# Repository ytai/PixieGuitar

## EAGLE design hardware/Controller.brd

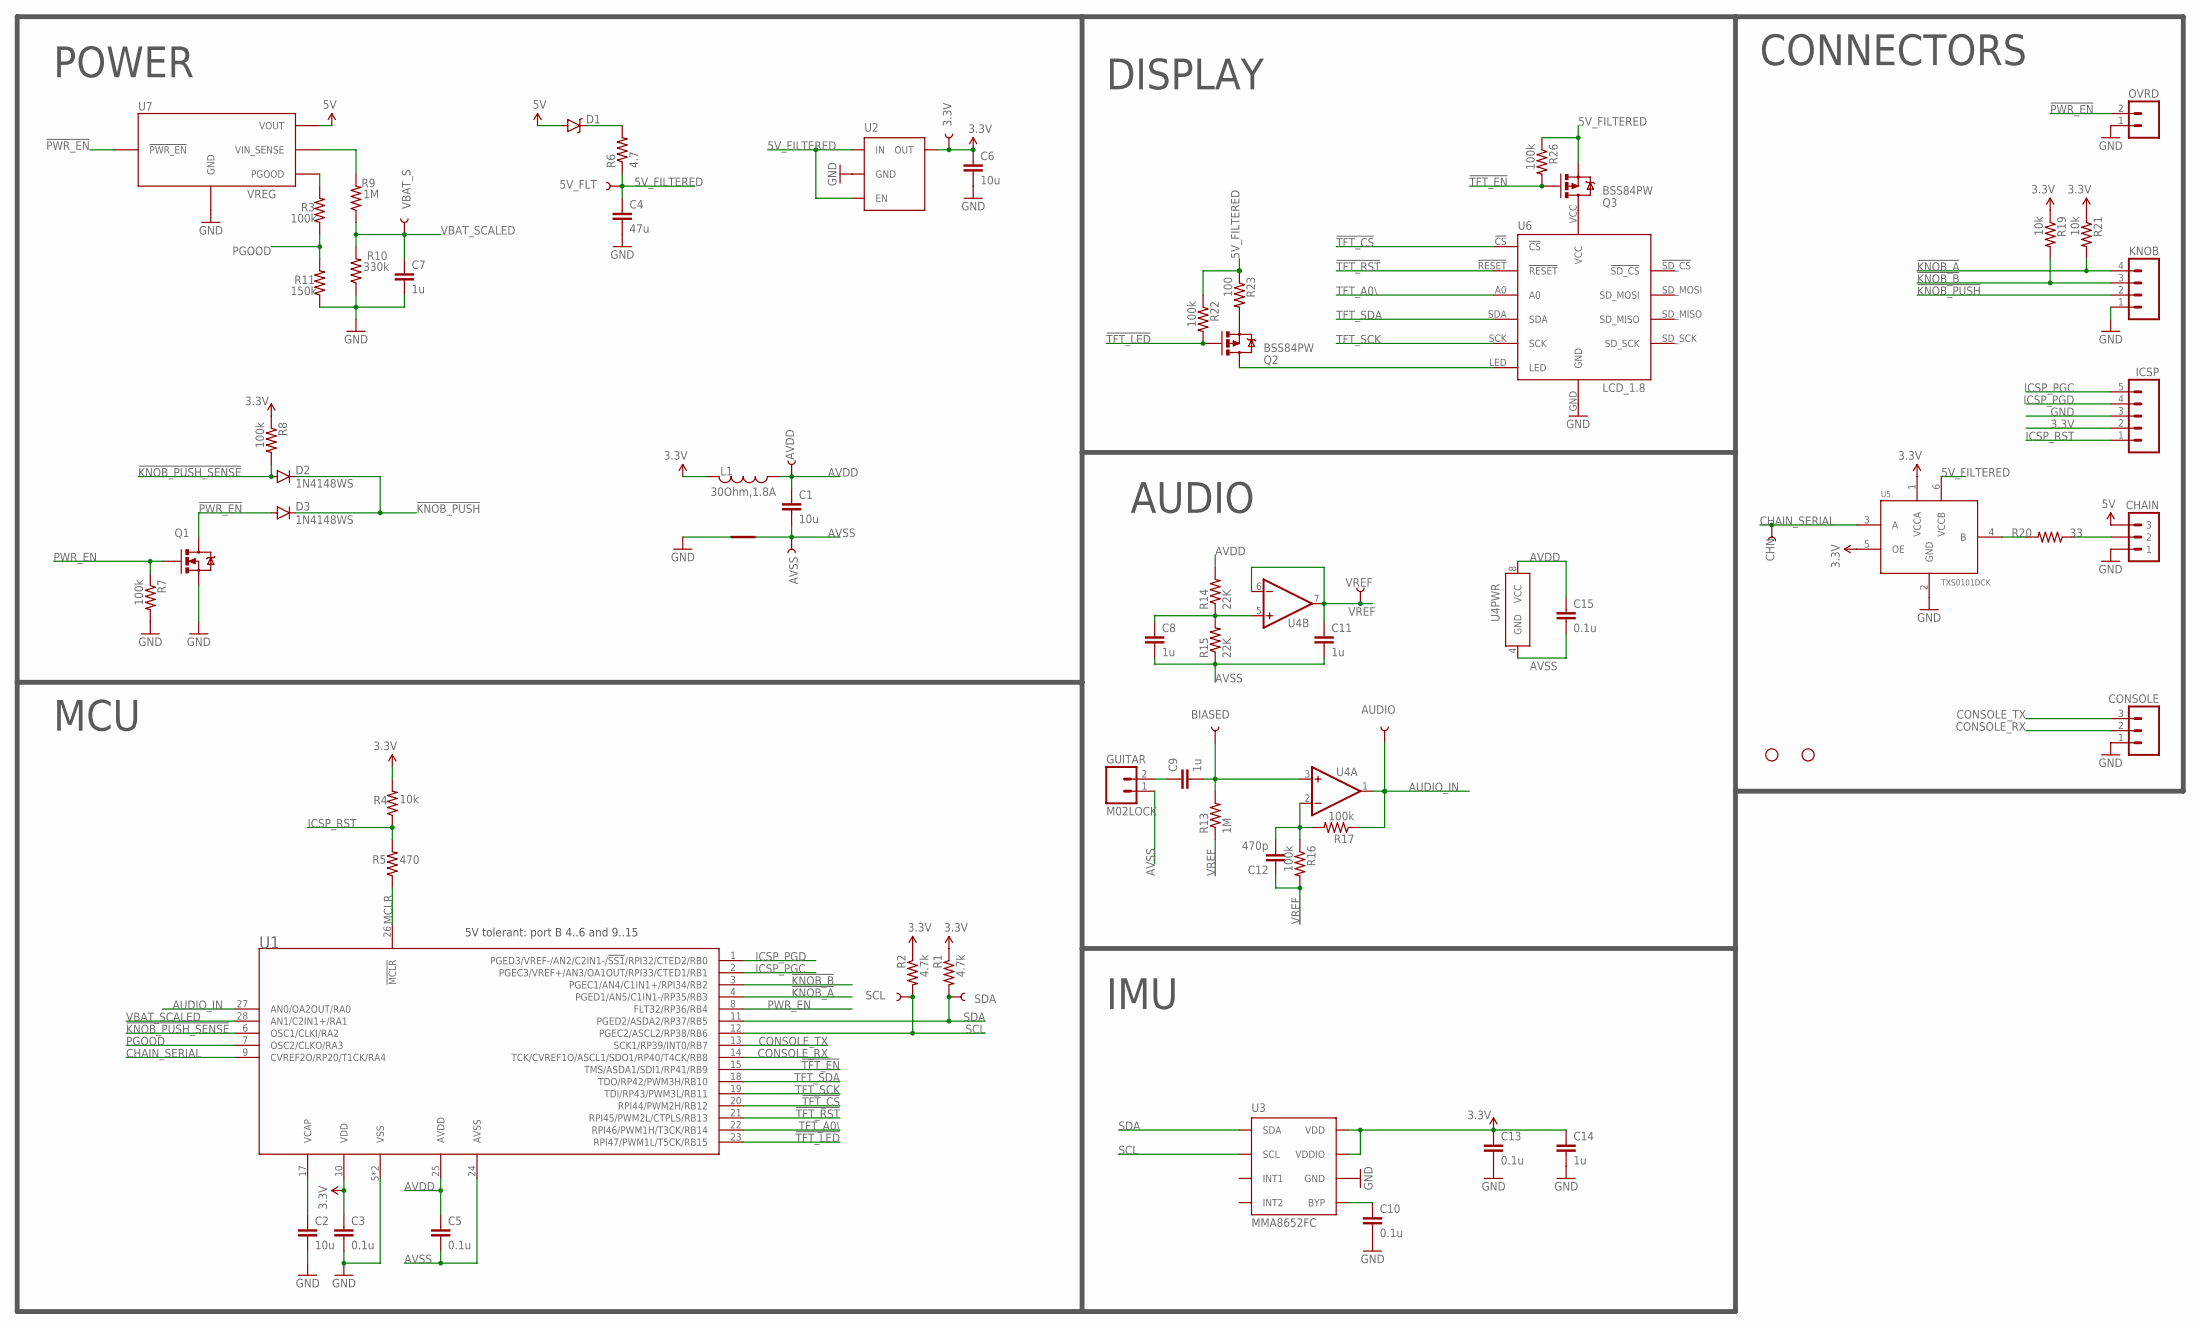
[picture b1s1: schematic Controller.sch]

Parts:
3.3V, 5V_FLT: TEST-POINT3; PAD.03X.03
AUDIO: TEST-POINT3; PAD.03X.03
AVDD: TEST-POINT3; PAD.03X.03
AVSS: TEST-POINT3; PAD.03X.03
BIASED: TEST-POINT3; PAD.03X.03
C1, C2: 10u; 0805
C3, C5, C10, C13, C15: 0.1u; 0603-CAP
C4: 47u; 1206
C6: 10u; 0603-CAP
C7, C8, C9, C11, C14: 1u; 0603-CAP
C12: 470p; 0603-CAP
CHAIN: M030.1PWR+SIG; 1X03-0.1PWR+SIG
CHN: TEST-POINT3; PAD.03X.03
CONSOLE: M03LOCK; 1X03_LOCK
D1: DB2J20900L; SOD-323
D2, D3: 1N4148WS; SOD-323
GUITAR: M02LOCK; 1X02_LOCK
ICSP: M05LOCK; 1X05_LOCK
JP1, JP2: STAND-OFF
KNOB: M04LOCK; 1X04_LOCK
L1: 30Ohm,1.8A; 0603
OVRD: M02LOCK; 1X02_LOCK
Q1: MOSFET-NCHANNEL2N7002PW; SOT323
Q2, Q3: BSS84PW; SOT323
R1, R2: 4.7k; 0603-RES
R3, R7, R8, R16, R17, R22, R26: 100k; 0603-RES
R4, R19, R21: 10k; 0603-RES
R5: 470; 0603-RES
R6: 4.7; 0603-RES
R9, R13: 1M; 0603-RES
R10: 330k; 0603-RES
R11: 150k; 0603-RES
R14, R15: 22K; 0603-RES
R20: 33; 0603-RES
R23: 100; 0603-RES
SCL: TEST-POINT3; PAD.03X.03
SDA: TEST-POINT3; PAD.03X.03
SH1: SHORT; SHORT_TOP-8
U1: DSPIC33EPXXXMC202/502/PT; QFN-S-28
U2: MIC5365YC5; SC70
U3: MMA8652FC; 10-VFDFN
U4: MCP6002MS; MSOP-8
U5: TXS0101DCK; SC70-6
U6: LCD_1.8
U7: VREG
VBAT_S: TEST-POINT3; PAD.03X.03
VREF: TEST-POINT3; PAD.03X.03

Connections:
3.3V: 3.3V.P$1, C3.1, C6.1, C13.1, C14.1, ICSP.2, L1.2, R1.1, R2.1, R4.2, R8.1, R19.1, R21.1, U1.10 (VDD), U2.5 (OUT), U3.1 (VDD), U3.8 (VDDIO), U5.1 (VCCA), U5.5 (OE)
5V: CHAIN.P$3 (3), D1.A, U7.VOUT
5V_FILTERED: 5V_FLT.P$1, C4.1, Q3.2 (S), R6.1, R22.1, R23.1, R26.1, U2.1 (IN), U2.3 (EN), U5.6 (VCCB)
!KNOB_A: KNOB.4, R21.2, U1.4 (PGED1/AN5/C1IN1-/RP35/RB3)
!KNOB_B: KNOB.3, R19.2, U1.3 (PGEC1/AN4/C1IN1+/RPI34/RB2)
!KNOB_PUSH: D2.C, D3.C, KNOB.2
!KNOB_PUSH_SENSE: D2.A, R8.2, U1.6 (OSC1/CLKI/RA2)
!PWR_EN: D3.A, OVRD.2, Q1.3 (D), U7.!EN (!PWR_EN)
!TFT_CS: U1.20 (RPI44/PWM2H/RB12), U6.!CS
!TFT_EN: Q3.1 (G), R26.2, U1.15 (TMS/ASDA1/SDI1/RP41/RB9)
!TFT_LED: Q2.1 (G), R22.2, U1.23 (RPI47/PWM1L/T5CK/RB15)
!TFT_RST: U1.21 (RPI45/PWM2L/CTPLS/RB13), U6.!RESET
AUDIO_IN: AUDIO.P$1, R17.1, U1.27 (AN0/OA2OUT/RA0), U4.1 (OUT)
AVDD: AVDD.P$1, C1.1, C5.1, C15.1, L1.1, R14.2, U1.25 (AVDD), U4.8 (VCC)
AVSS: AVSS.P$1, C1.2, C5.2, C8.2, C11.2, C15.2, GUITAR.1, R15.1, SH1.2, U1.24 (AVSS), U4.4 (GND)
CHAIN_SERIAL: CHN.P$1, U1.9 (CVREF2O/RP20/T1CK/RA4), U5.3 (A)
CONSOLE_RX: CONSOLE.2, U1.14 (TCK/CVREF1O/ASCL1/SDO1/RP40/T4CK/RB8)
CONSOLE_TX: CONSOLE.3, U1.13 (SCK1/RP39/INT0/RB7)
GND: C2.2, C3.2, C4.2, C6.2, C7.2, C10.2, C13.2, C14.2, CHAIN.P$1 (1), CONSOLE.1, ICSP.3, KNOB.1, OVRD.1, Q1.2 (S), R7.2, R10.1, R11.1, SH1.1, U1.5 (VSS), U1.16 (VSS), U2.2 (GND), U3.6 (GND), U3.7 (GND), U3.9 (GND), U5.2 (GND), U6.GND, U7.GND_OUT (GND)
ICSP_PGC: ICSP.5, U1.2 (PGEC3/VREF+/AN3/OA1OUT/RPI33/CTED1/RB1)
ICSP_PGD: ICSP.4, U1.1 (PGED3/VREF-/AN2/C2IN1-/!SS1!/RPI32/CTED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)
ICSP_RST: ICSP.1, R4.1, R5.2
MCLR: R5.1, U1.26 (!MCLR)
unnamed: C8.1, R14.1, R15.2, U4.5 (+IN)
unnamed: D1.C, R6.2
unnamed: C9.1, GUITAR.2
unnamed: C12.2, R16.1, R17.2, U4.2 (-IN)
unnamed: C2.1, U1.17 (VCAP)
unnamed: R20.2, U5.4 (B)
unnamed: BIASED.P$1, C9.2, R13.2, U4.3 (+IN)
unnamed: R3.2, U7.PGOOD
unnamed: Q2.3 (D), U6.LED
unnamed: Q3.3 (D), U6.VCC
unnamed: Q2.2 (S), R23.2
unnamed: C10.1, U3.4 (BYP)
unnamed: CHAIN.P$2 (2), R20.1
PGOOD: R3.1, R11.2, U1.7 (OSC2/CLKO/RA3)
PWR_EN: Q1.1 (G), R7.1, U1.8 (FLT32/RP36/RB4)
SCL: R2.2, SCL.P$1, U1.12 (PGEC2/ASCL2/RP38/RB6), U3.2 (SCL)
SDA: R1.2, SDA.P$1, U1.11 (PGED2/ASDA2/RP37/RB5), U3.10 (SDA)
TFT_A0\: U1.22 (RPI46/PWM1H/T3CK/RB14), U6.A0
TFT_SCK: U1.19 (TDI/RP43/PWM3L/RB11), U6.SCK
TFT_SDA: U1.18 (TDO/RP42/PWM3H/RB10), U6.SDA
VBAT_SCALED: C7.1, R9.1, R10.2, U1.28 (AN1/C2IN1+/RA1), VBAT_S.P$1
VBAT_SENSE: R9.2, U7.VSENSE (VIN_SENSE)
VREF: C11.1, C12.1, R13.1, R16.2, U4.6 (-IN), U4.7 (OUT), VREF.P$1

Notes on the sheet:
5V tolerant: port B 4..6 and 9..15
POWER
IMU
AUDIO
DISPLAY
CONNECTORS
MCU

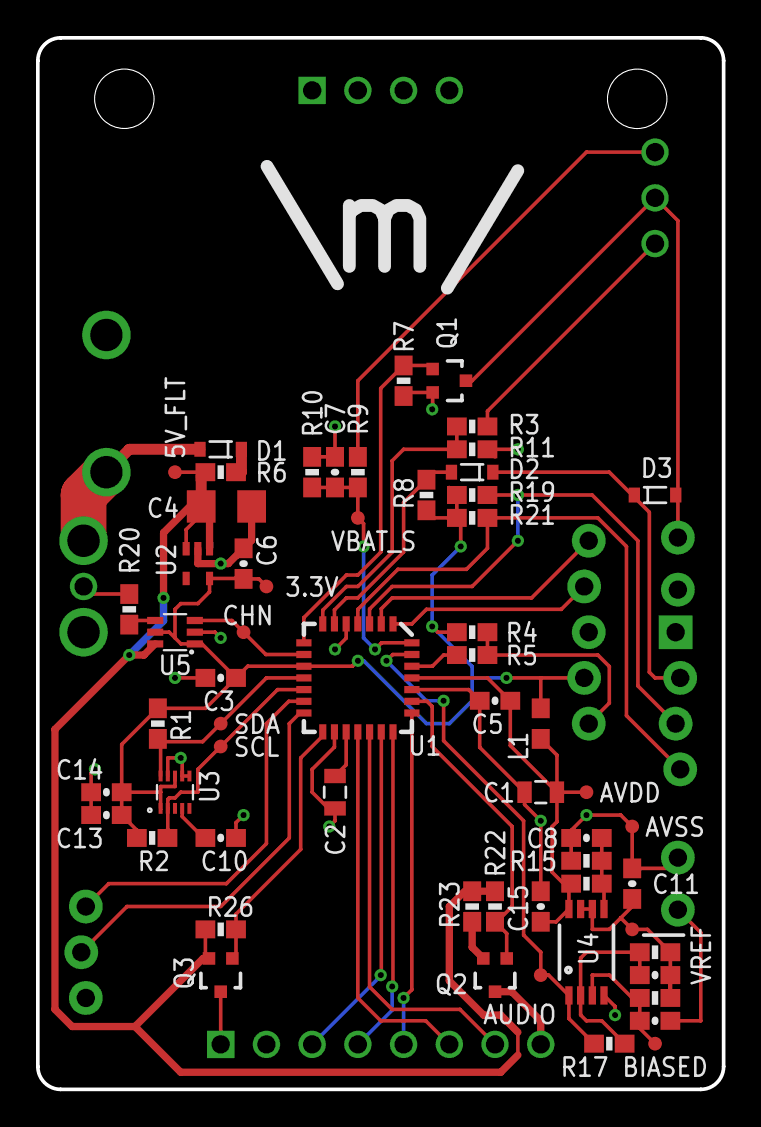
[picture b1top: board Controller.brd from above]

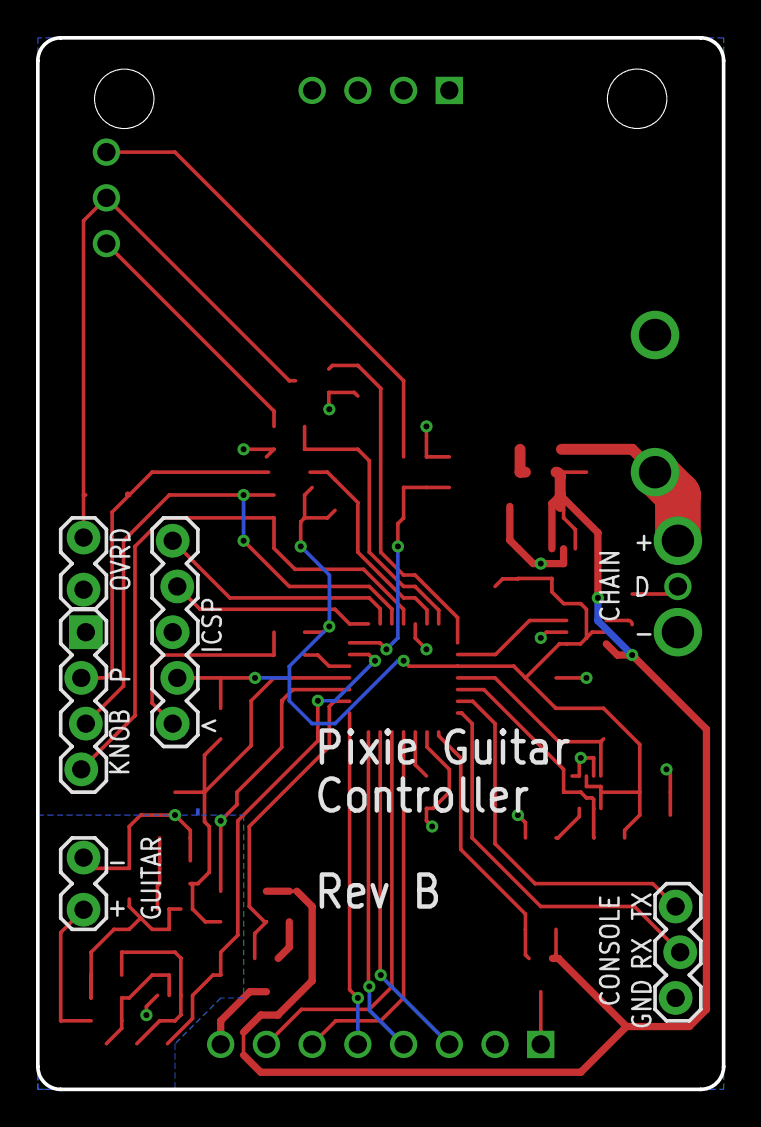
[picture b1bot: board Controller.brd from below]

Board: 2 copper layers, 38.1 x 58.4 mm, 71 parts (8 on the bottom side), 46 nets.

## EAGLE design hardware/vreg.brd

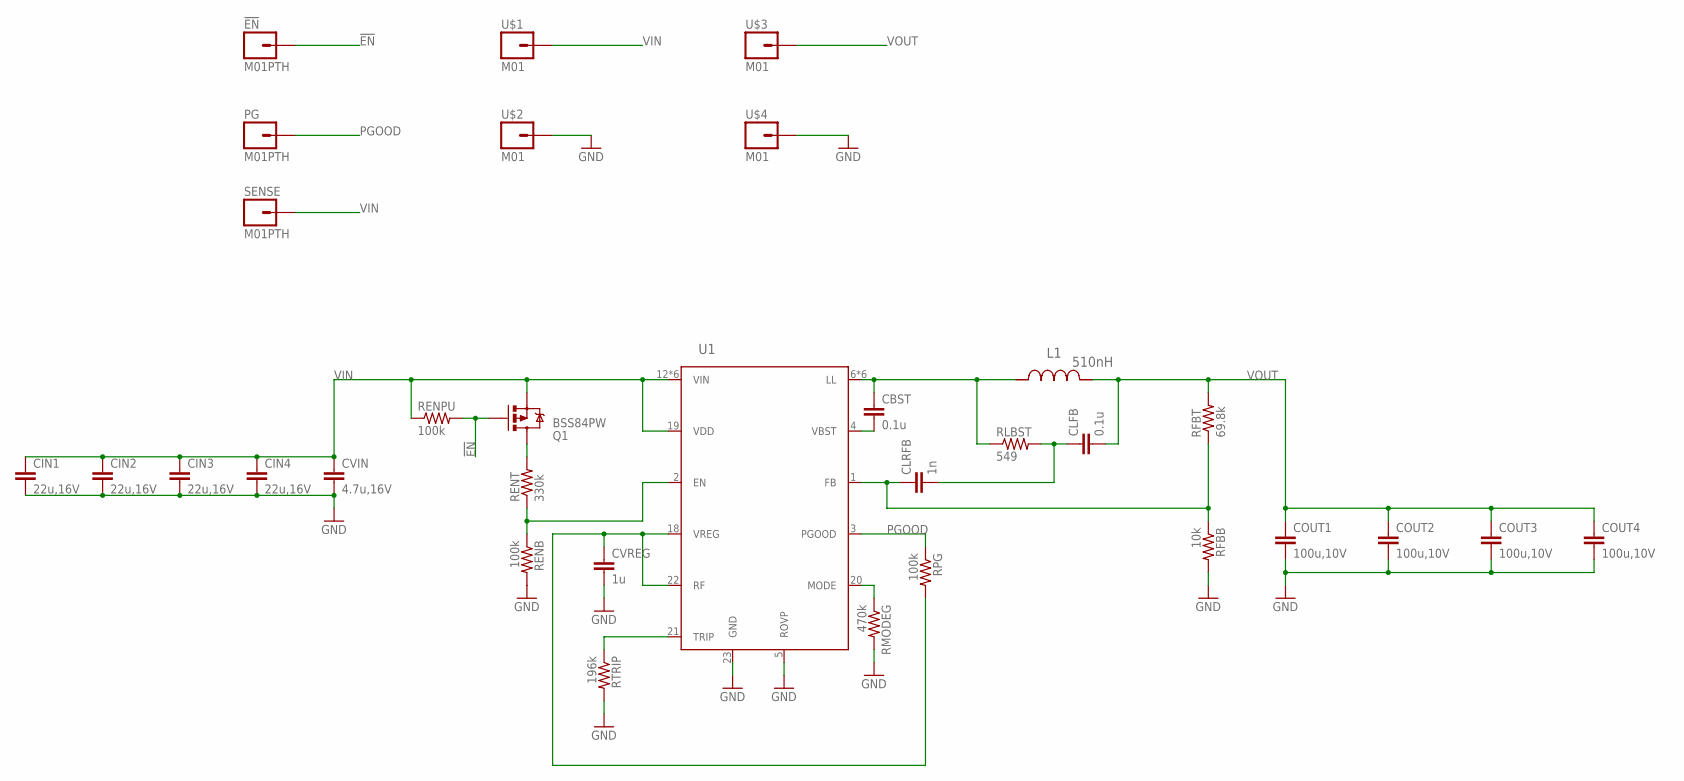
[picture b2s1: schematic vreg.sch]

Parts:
!EN: M01PTH; 1X01
CBST: 0.1u; 0603-CAP
CIN1, CIN2, CIN3, CIN4: 22u,16V; 1210
CLFB: 0.1u; 0603-CAP
CLRFB: 1n; 0603-CAP
COUT1, COUT2, COUT3, COUT4: 100u,10V; 1210
CVIN: 4.7u,16V; 1206
CVREG: 1u; 0603-CAP
L1: 510nH; FP1107
PG: M01PTH; 1X01
Q1: BSS84PW; SOT323
RENB: 100k; 0603-RES
RENPU: 100k; 0603-RES
RENT: 330k; 0603-RES
RFBB: 10k; 0603-RES
RFBT: 69.8k; 0603-RES
RLBST: 549; 0603-RES
RMODEG: 470k; 0603-RES
RPG: 100k; 0603-RES
RTRIP: 196k; 0603-RES
SENSE: M01PTH; 1X01
U1: TPS53319DQPR; DQP0022A
U$1, U$2, U$3, U$4: M01; PIN_16AWG

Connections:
!EN: !EN.1, Q1.1 (G), RENPU.2
GND: CIN1.2, CIN2.2, CIN3.2, CIN4.2, COUT1.2, COUT2.2, COUT3.2, COUT4.2, CVIN.2, CVREG.2, RENB.2, RFBB.2, RMODEG.2, RTRIP.2, U1.5 (ROVP), U1.23 (GND), U$2.1, U$4.1
LL: CBST.1, L1.1, RLBST.1, U1.6 (LL), U1.7 (LL), U1.8 (LL), U1.9 (LL), U1.10 (LL), U1.11 (LL)
unnamed: RMODEG.1, U1.20 (MODE)
unnamed: RENB.1, RENT.1, U1.2 (EN)
unnamed: Q1.3 (D), RENT.2
unnamed: CVREG.1, RPG.2, U1.18 (VREG), U1.22 (RF)
unnamed: RTRIP.1, U1.21 (TRIP)
unnamed: CBST.2, U1.4 (VBST)
unnamed: CLFB.1, CLRFB.2, RLBST.2
unnamed: CLRFB.1, RFBB.1, RFBT.1, U1.1 (FB)
PGOOD: PG.1, RPG.1, U1.3 (PGOOD)
VIN: CIN1.1, CIN2.1, CIN3.1, CIN4.1, CVIN.1, Q1.2 (S), RENPU.1, SENSE.1, U1.12 (VIN), U1.13 (VIN), U1.14 (VIN), U1.15 (VIN), U1.16 (VIN), U1.17 (VIN), U1.19 (VDD), U$1.1
VOUT: CLFB.2, COUT1.1, COUT2.1, COUT3.1, COUT4.1, L1.2, RFBT.2, U$3.1

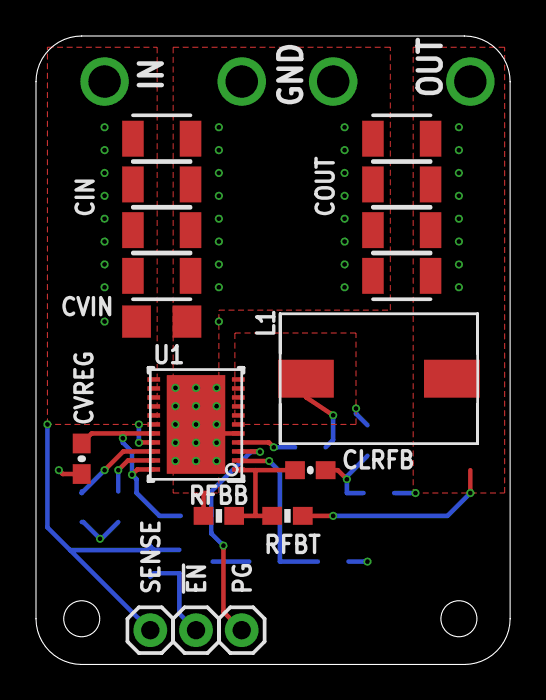
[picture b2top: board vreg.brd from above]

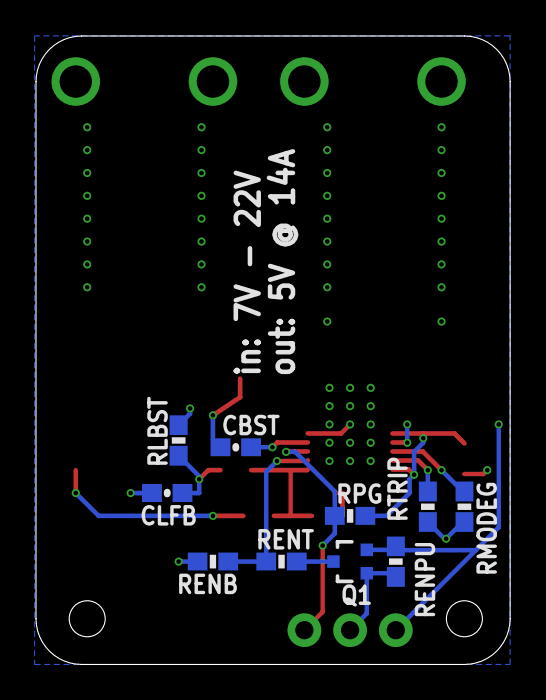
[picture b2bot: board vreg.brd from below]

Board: 4 copper layers, 26.3 x 34.9 mm, 32 parts (10 on the bottom side), 14 nets.

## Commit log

2015-12-07 Initial commit - voltage regulator
2016-01-06 Initial commit of the controller board
2016-01-06 Commit the gerbers for Controller rev A
2016-01-26 hardware: Change in resistor values in analog section
2016-02-16 Add docs
2016-02-16 hardware: Add ERRATA
2016-02-16 hardware: One of the test-points wasn't routed
2016-02-16 hardware: Remove R18
    It was wrong to pull to 3.3V behind the diode, resulting in always enabling the VREG
2016-02-16 hardware: Route TFT SPI pins to RPx pins
    Previously, the MCU pins used for TFT SPI could not be driven by a SPI peripheral.
2016-02-16 hardware: divide PGOOD to be 3.3V
    It is a 5V signal, previously fed into a non-5V tolerant pin.
2016-02-16 hardware: Bump revision number to B
2016-02-16 hardware: CAM files for controller rev. B
2016-02-16 hardware: Round controller board corners
2016-03-21 draft app
2016-04-24 Refactor app framework
    A more generic application framework supporting multiple different applications.
2016-04-24 Remove small warning
2016-04-26 Fix integer constant overflow in ticker
2016-04-26 Introduce clipping regions
    Allows specifying graphics relative to a region of the screen.
2016-04-28 Text widgets can trigger commands
    Includes slight change in the command API.
    This now exercises the application push/pop stack.
2016-04-28 Macro rename
2016-04-28 First stab at a widget system
2016-04-28 Text widget dimensions are provided
2016-04-28 Support HSV and a colorful menu
2016-04-28 Add TODOs
2016-05-01 Remove explicit instance pointers in objects
2016-05-02 Add title bar
    Also, made some changes to how application drawing is done:
    Screen is no longer cleared by the framework upon resume, it is
    now the app's responsibility.
    The title bar persists across apps.
2016-05-02 Improve menu colors
2016-05-17 software: Add Pseudorandom Number Generator
2016-05-17 software: Extract color utilities
2016-05-17 software: Use PRNG in demo app
    Choose a random LED each step
2016-05-17 software: Rename / move main menu and widget app
2016-05-17 software: Add rainbow app
2016-05-17 software: Always check battery voltage
    This is no longer an app request, since we need this for the framework
    (title bar, auto-off).
2016-05-17 software: Add hysteresis on SoC
2016-05-17 software: Small refactoring around TextWidget
2016-05-17 software: Add power off menu item
2016-05-17 software: Preliminary audio processing module
    The implementation still needs improvements, but the API is probably
    fine.
2016-05-17 software: Add number widget
2016-05-17 software: Change accelerometer handling, screen flipping and app redraw
    - App now gets the neck tilt in degrees rather than raw acc reading.
    - Framework handles flipping the screen. As result, the force redraw
    signal needs to be generated by the framework and it turns out that
    it is anyway better than having every app implement the same logic.
2016-05-17 software: Refactor commands to be value types
    Added a NOP command to replace NULL.
2016-05-17 Organized TODOs
2016-05-17 software: Add enum widget
2016-05-17 software: Small refactor around VerticalWidgetList
2016-05-17 software: Rename util to shell_util
2016-05-17 software: A few more palettes
2016-05-17 software: Remove SoC value from app tick
2016-05-17 software: Add color constants
2016-05-17 software: Add palettes to rainbow app
2016-05-17 software: Move "Exit" to the end on rainbow app
2016-05-17 software: Fix bug in vertical widget list
    Would not wrap around the start.
2016-05-17 software: Improved rainbow app
    Added some settings
2016-05-17 software: IMU improvements
    - Catch IMU hangs.
    - Better calculation of tilt angles.
2016-05-17 software: Add lightning strike to rainbow app
2016-05-17 software: Extract bar chart component
2016-05-17 software: Centralized handling of chain
    App task now writes to the chain every tick, so it turns
    off immediately when exiting apps. It also saves each app
    from having to have its own buffer.
2016-05-17 software: Add spinner app
2016-05-17 software: Add power measurement
2016-05-17 software: Misc cleanups
2016-05-18 software: Add fireworks app
2016-05-18 software: Power off on empty battery
2016-05-18 software: Nit fix
2016-05-18 software: Added splash up
    Protection against inadvertent power up
2016-05-18 software: Organize main menu
2016-05-27 software: Reduce tilt sensitivity in apps

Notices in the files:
parts and their libraries:
SparkFun-Passives: Licensing: CC v3.0 Share-Alike You are welcome to use this library for commercial purposes.
SparkFun-Connectors: Licensing: Creative Commons ShareAlike 4.0 International - https://creativecommons.org/licenses/by-sa/4.0
